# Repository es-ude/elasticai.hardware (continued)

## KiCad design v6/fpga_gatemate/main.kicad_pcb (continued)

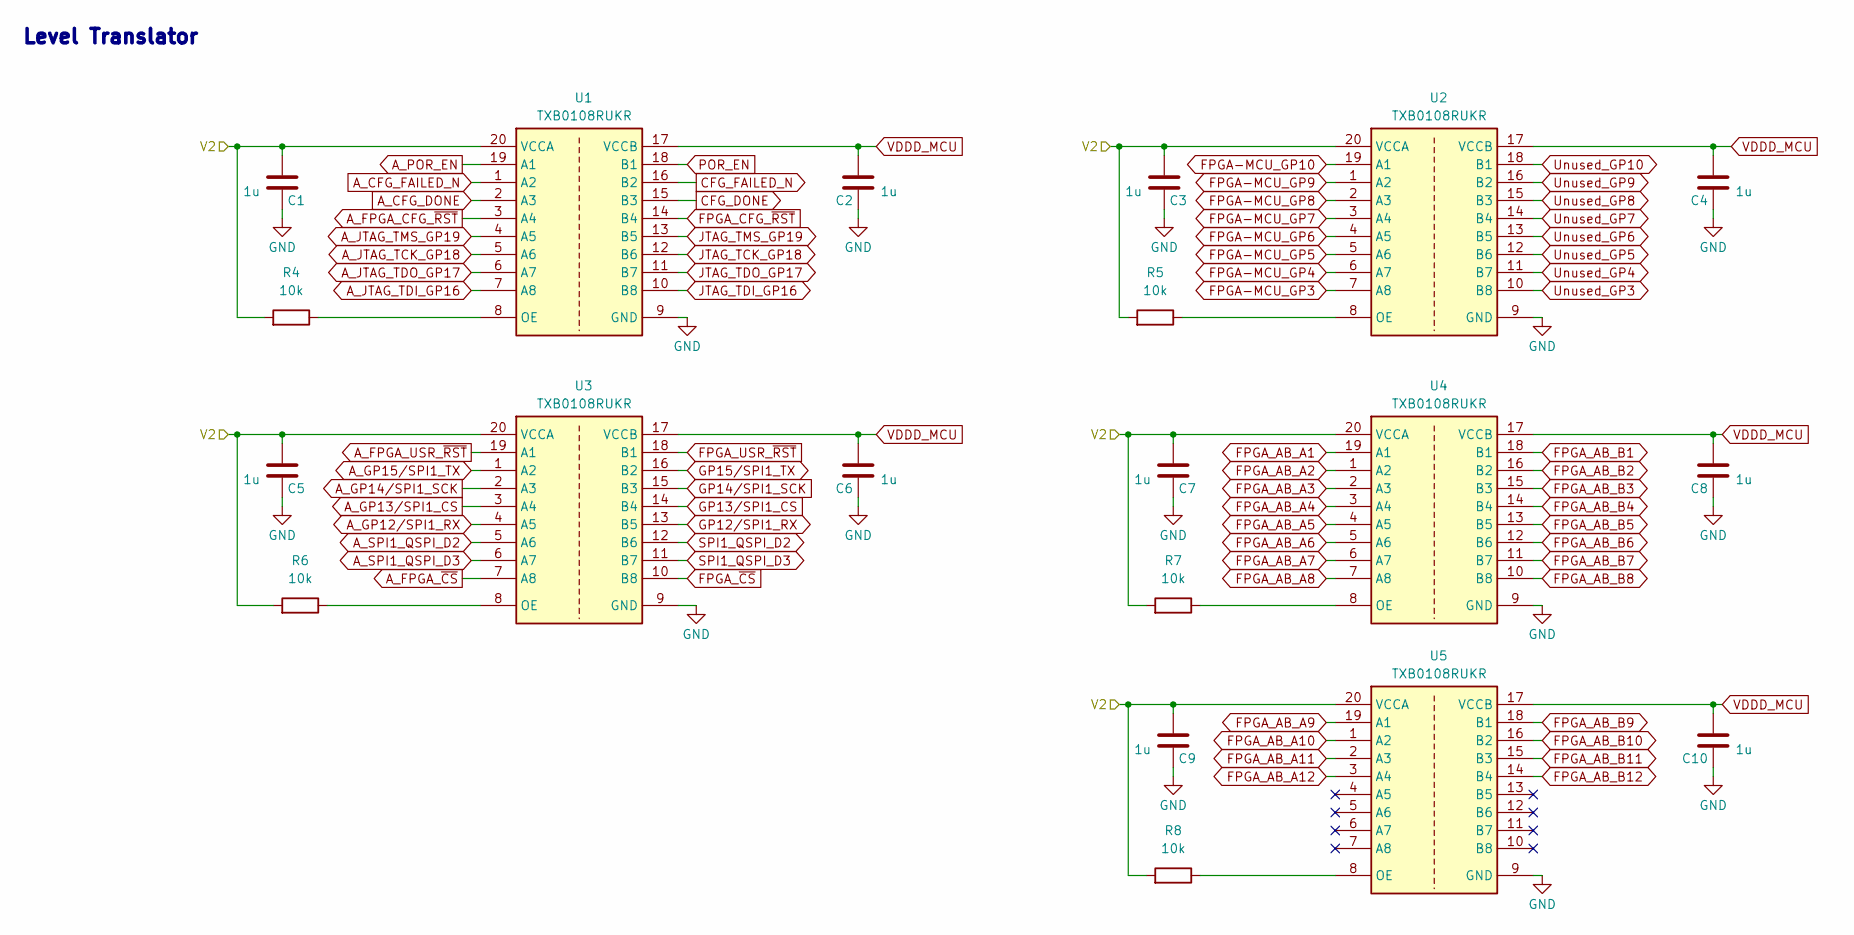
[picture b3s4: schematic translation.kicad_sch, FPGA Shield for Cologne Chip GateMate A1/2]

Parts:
C1, C2, C3, C4, C5, C6, C7, C8, C9, C10: 1u; C_0402_1005Metric
R4, R5, R6, R7, R8: 10k; R_0402_1005Metric
U1, U2, U3, U4, U5: TXB0108RUKR; WQFN-20-1EP_3x3mm_P0.4mm_EP1.7x1.7mm_TI_RUK0020; Manufacturer_Part_Number TXB0108RUKR

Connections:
/2V5: C1.2, C3.2, C5.2, C7.2, C9.2, R4.2, R5.2, R6.2, R7.2, R8.2, U1.20 (VCCA), U2.20 (VCCA), U3.20 (VCCA), U4.20 (VCCA), U5.20 (VCCA); also elsewhere on the board
A_CFG_DONE: U1.2 (A3); also elsewhere on the board
A_CFG_FAILED_N: U1.1 (A2); also elsewhere on the board
A_FPGA_CFG_~RST: U1.3 (A4); also elsewhere on the board
A_FPGA_USR_~RST: U3.19 (A1); also elsewhere on the board
A_FPGA_~CS: U3.7 (A8); also elsewhere on the board
A_GP12/SPI1_RX: U3.4 (A5); also elsewhere on the board
A_GP13/SPI1_CS: U3.3 (A4); also elsewhere on the board
A_GP14/SPI1_SCK: U3.2 (A3); also elsewhere on the board
A_GP15/SPI1_TX: U3.1 (A2); also elsewhere on the board
A_JTAG_TCK_GP18: U1.5 (A6); also elsewhere on the board
A_JTAG_TDI_GP16: U1.7 (A8); also elsewhere on the board
A_JTAG_TDO_GP17: U1.6 (A7); also elsewhere on the board
A_JTAG_TMS_GP19: U1.4 (A5); also elsewhere on the board
A_POR_EN: U1.19 (A1); also elsewhere on the board
A_SPI1_QSPI_D2: U3.5 (A6); also elsewhere on the board
A_SPI1_QSPI_D3: U3.6 (A7); also elsewhere on the board
CFG_DONE: U1.15 (B3); also elsewhere on the board
CFG_FAILED_N: U1.16 (B2); also elsewhere on the board
FPGA-MCU_GP3: U2.7 (A8); also elsewhere on the board
FPGA-MCU_GP4: U2.6 (A7); also elsewhere on the board
FPGA-MCU_GP5: U2.5 (A6); also elsewhere on the board
FPGA-MCU_GP6: U2.4 (A5); also elsewhere on the board
FPGA-MCU_GP7: U2.3 (A4); also elsewhere on the board
FPGA-MCU_GP8: U2.2 (A3); also elsewhere on the board
FPGA-MCU_GP9: U2.1 (A2); also elsewhere on the board
FPGA-MCU_GP10: U2.19 (A1); also elsewhere on the board
FPGA_AB_A1: U4.19 (A1); also elsewhere on the board
FPGA_AB_A2: U4.1 (A2); also elsewhere on the board
FPGA_AB_A3: U4.2 (A3); also elsewhere on the board
FPGA_AB_A4: U4.3 (A4); also elsewhere on the board
FPGA_AB_A5: U4.4 (A5); also elsewhere on the board
FPGA_AB_A6: U4.5 (A6); also elsewhere on the board
FPGA_AB_A7: U4.6 (A7); also elsewhere on the board
FPGA_AB_A8: U4.7 (A8); also elsewhere on the board
FPGA_AB_A9: U5.19 (A1); also elsewhere on the board
FPGA_AB_A10: U5.1 (A2); also elsewhere on the board
FPGA_AB_A11: U5.2 (A3); also elsewhere on the board
FPGA_AB_A12: U5.3 (A4); also elsewhere on the board
FPGA_AB_B1: U4.18 (B1); also elsewhere on the board
FPGA_AB_B2: U4.16 (B2); also elsewhere on the board
FPGA_AB_B3: U4.15 (B3); also elsewhere on the board
FPGA_AB_B4: U4.14 (B4); also elsewhere on the board
FPGA_AB_B5: U4.13 (B5); also elsewhere on the board
FPGA_AB_B6: U4.12 (B6); also elsewhere on the board
FPGA_AB_B7: U4.11 (B7); also elsewhere on the board
FPGA_AB_B8: U4.10 (B8); also elsewhere on the board
FPGA_AB_B9: U5.18 (B1); also elsewhere on the board
FPGA_AB_B10: U5.16 (B2); also elsewhere on the board
FPGA_AB_B11: U5.15 (B3); also elsewhere on the board
FPGA_AB_B12: U5.14 (B4); also elsewhere on the board
FPGA_CFG_~RST: U1.14 (B4); also elsewhere on the board
FPGA_USR_~RST: U3.18 (B1); also elsewhere on the board
FPGA_~CS: U3.10 (B8); also elsewhere on the board
GND: C1.1, C2.1, C3.1, C4.1, C5.1, C6.1, C7.1, C8.1, C9.1, C10.1, U1.9 (GND), U1.21 (GND), U2.9 (GND), U2.21 (GND), U3.9 (GND), U3.21 (GND), U4.9 (GND), U4.21 (GND), U5.9 (GND), U5.21 (GND); also elsewhere on the board
GP12/SPI1_RX: U3.13 (B5); also elsewhere on the board
GP13/SPI1_CS: U3.14 (B4); also elsewhere on the board
GP14/SPI1_SCK: U3.15 (B3); also elsewhere on the board
GP15/SPI1_TX: U3.16 (B2); also elsewhere on the board
JTAG_TCK_GP18: U1.12 (B6); also elsewhere on the board
JTAG_TDI_GP16: U1.10 (B8); also elsewhere on the board
JTAG_TDO_GP17: U1.11 (B7); also elsewhere on the board
JTAG_TMS_GP19: U1.13 (B5); also elsewhere on the board
unnamed: R4.1, U1.8 (OE)
unnamed: R5.1, U2.8 (OE)
unnamed: R6.1, U3.8 (OE)
unnamed: R7.1, U4.8 (OE)
unnamed: R8.1, U5.8 (OE)
POR_EN: U1.18 (B1); also elsewhere on the board
SPI1_QSPI_D2: U3.12 (B6); also elsewhere on the board
SPI1_QSPI_D3: U3.11 (B7); also elsewhere on the board
Unused_GP3: U2.10 (B8); also elsewhere on the board
Unused_GP4: U2.11 (B7); also elsewhere on the board
Unused_GP5: U2.12 (B6); also elsewhere on the board
Unused_GP6: U2.13 (B5); also elsewhere on the board
Unused_GP7: U2.14 (B4); also elsewhere on the board
Unused_GP8: U2.15 (B3); also elsewhere on the board
Unused_GP9: U2.16 (B2); also elsewhere on the board
Unused_GP10: U2.18 (B1); also elsewhere on the board
VDDD_MCU: C2.2, C4.2, C6.2, C8.2, C10.2, U1.17 (VCCB), U2.17 (VCCB), U3.17 (VCCB), U4.17 (VCCB), U5.17 (VCCB); also elsewhere on the board

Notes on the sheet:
Level Translator

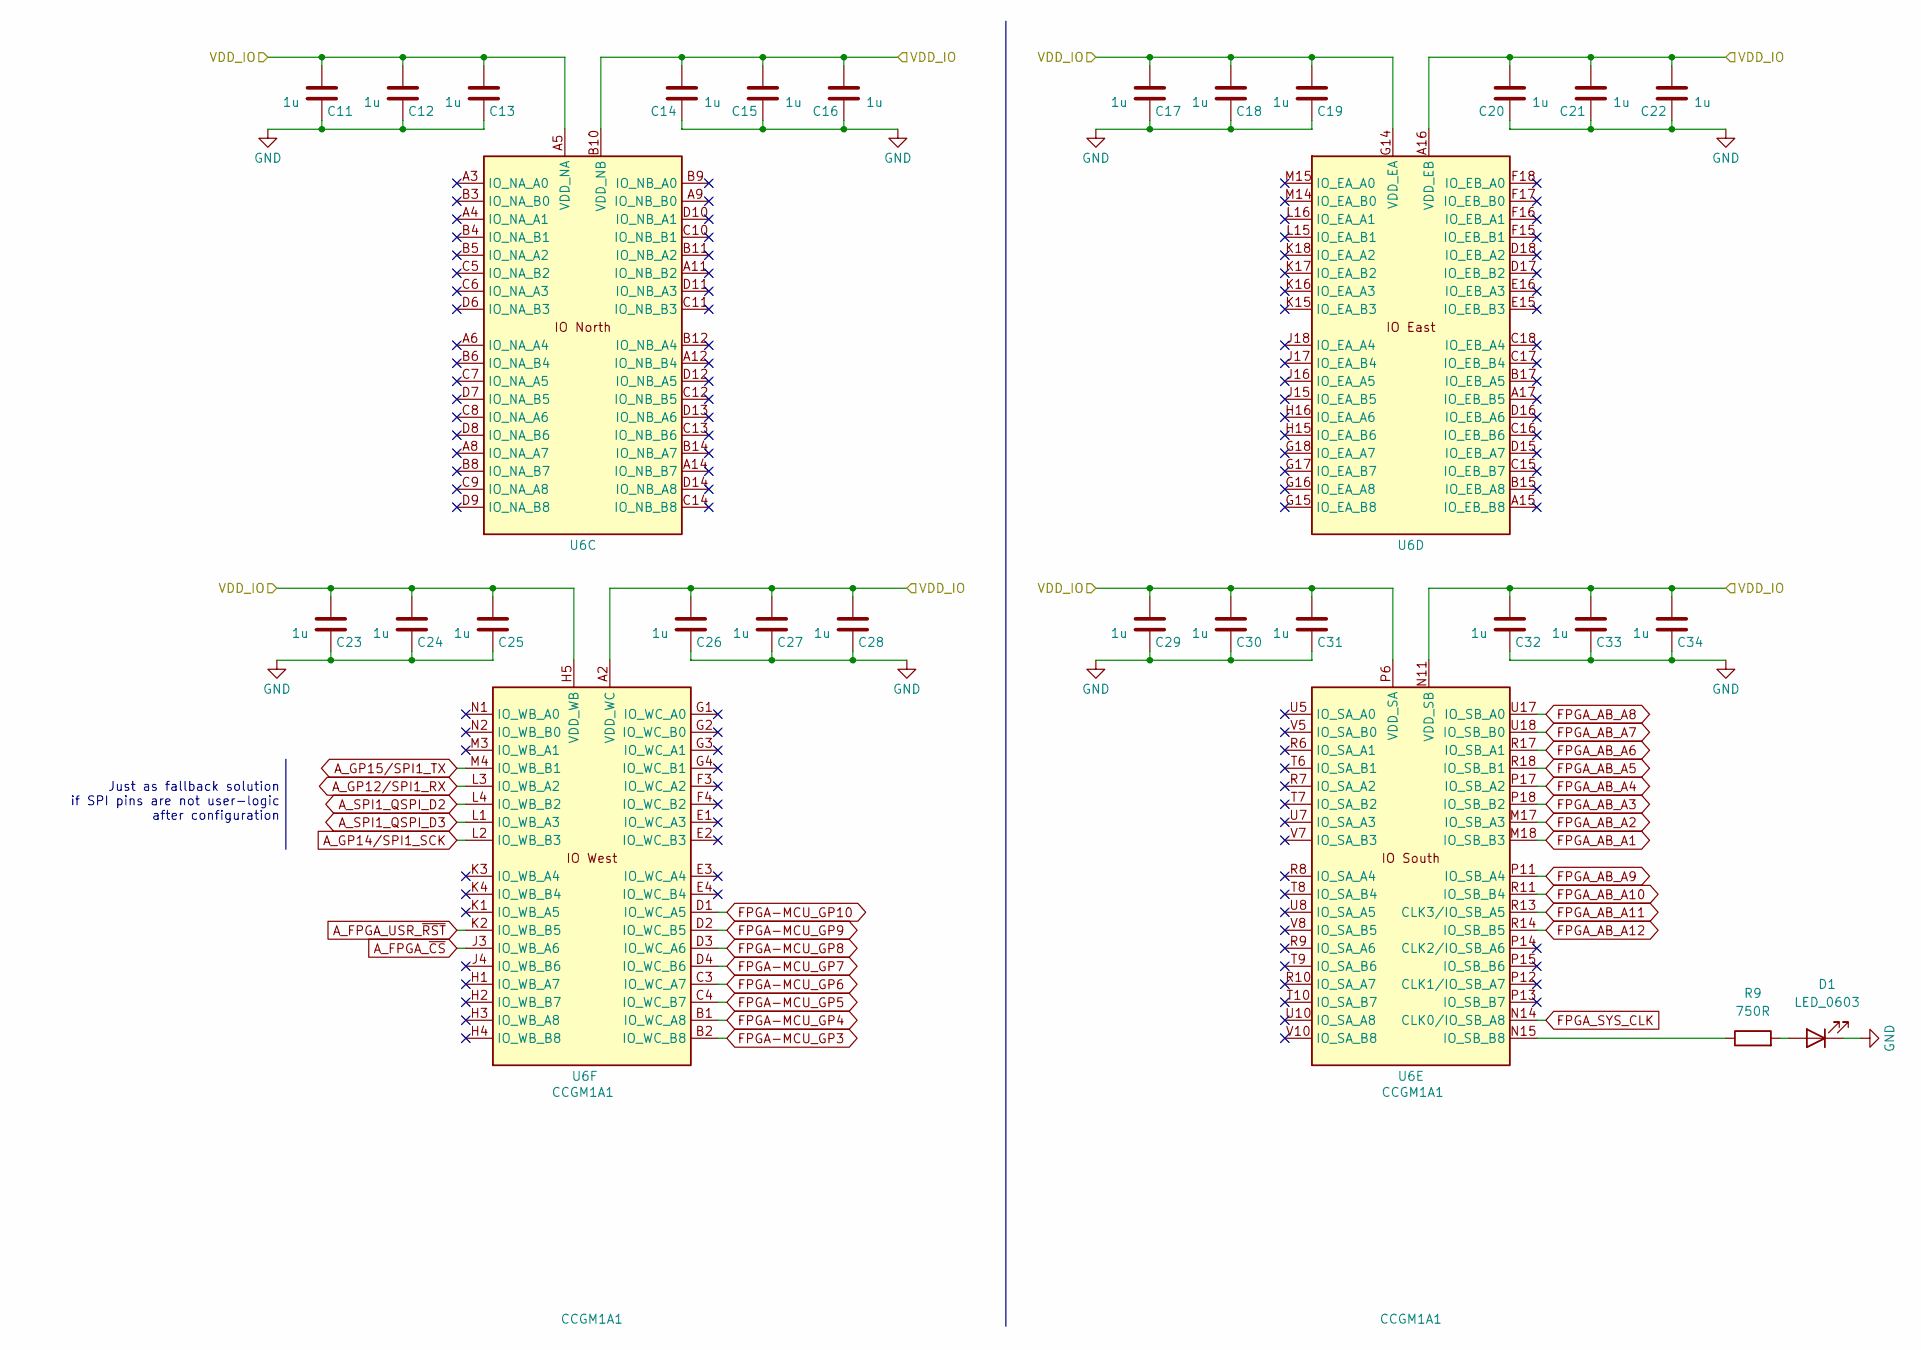
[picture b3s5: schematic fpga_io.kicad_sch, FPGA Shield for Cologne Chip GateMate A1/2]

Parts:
C11, C12, C13, C14, C15, C16, C17, C18, C19, C20, C21, C22, C23, C24, C25, C26, C27, C28, C29, C30, C31, C32, C33, C34: 1u; C_0402_1005Metric
D1: LED_0603; LED_0603_1608Metric
R9: 750R; R_0402_1005Metric
U6: CCGM1A1; BGA-324_15.0x15.0mm_Layout18x18_P0.8mm_Ball0.5mm_Pad0.4mm_N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

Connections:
/2V5: C11.2, C12.2, C13.2, C14.2, C15.2, C16.2, C17.2, C18.2, C19.2, C20.2, C21.2, C22.2, C23.2, C24.2, C25.2, C26.2, C27.2, C28.2, C29.2, C30.2, C31.2, C32.2, C33.2, C34.2, U6.A2 (VDD_WC), U6.A5 (VDD_NA), U6.A16 (VDD_EB), U6.B7 (VDD_NA), U6.B10 (VDD_NB), U6.B13 (VDD_NB), U6.B18 (VDD_EB), U6.C2 (VDD_WC), U6.D5 (VDD_WC), U6.E6 (VDD_NA), U6.E8 (VDD_NA), U6.E10 (VDD_NB), U6.E12 (VDD_NB), U6.E14 (VDD_EB), U6.E17 (VDD_EB), U6.F2 (VDD_WC), U6.F5 (VDD_WC), U6.F7 (VDD_NA), U6.F11 (VDD_NB), U6.F13 (VDD_EB), U6.G14 (VDD_EA), U6.H5 (VDD_WB), U6.H17 (VDD_EA), U6.J2 (VDD_WB), U6.J14 (VDD_EA), U6.K5 (VDD_WB), U6.L14 (VDD_EA), U6.L17 (VDD_EA), U6.M2 (VDD_WB), U6.M5 (VDD_WB), U6.N11 (VDD_SB), U6.N13 (VDD_SB), U6.N18 (VDD_SB), U6.P6 (VDD_SA), U6.P8 (VDD_SA), U6.P10 (VDD_SA), U6.R15 (VDD_SB), U6.T18 (VDD_SB), U6.U6 (VDD_SA), U6.U9 (VDD_SA); also elsewhere on the board
A_FPGA_USR_~RST: U6.K2 (IO_WB_B5); also elsewhere on the board
A_FPGA_~CS: U6.J3 (IO_WB_A6); also elsewhere on the board
A_GP12/SPI1_RX: U6.L3 (IO_WB_A2); also elsewhere on the board
A_GP14/SPI1_SCK: U6.L2 (IO_WB_B3); also elsewhere on the board
A_GP15/SPI1_TX: U6.M4 (IO_WB_B1); also elsewhere on the board
A_SPI1_QSPI_D2: U6.L4 (IO_WB_B2); also elsewhere on the board
A_SPI1_QSPI_D3: U6.L1 (IO_WB_A3); also elsewhere on the board
FPGA-MCU_GP3: U6.B2 (IO_WC_B8); also elsewhere on the board
FPGA-MCU_GP4: U6.B1 (IO_WC_A8); also elsewhere on the board
FPGA-MCU_GP5: U6.C4 (IO_WC_B7); also elsewhere on the board
FPGA-MCU_GP6: U6.C3 (IO_WC_A7); also elsewhere on the board
FPGA-MCU_GP7: U6.D4 (IO_WC_B6); also elsewhere on the board
FPGA-MCU_GP8: U6.D3 (IO_WC_A6); also elsewhere on the board
FPGA-MCU_GP9: U6.D2 (IO_WC_B5); also elsewhere on the board
FPGA-MCU_GP10: U6.D1 (IO_WC_A5); also elsewhere on the board
FPGA_AB_A1: U6.M18 (IO_SB_B3); also elsewhere on the board
FPGA_AB_A2: U6.M17 (IO_SB_A3); also elsewhere on the board
FPGA_AB_A3: U6.P18 (IO_SB_B2); also elsewhere on the board
FPGA_AB_A4: U6.P17 (IO_SB_A2); also elsewhere on the board
FPGA_AB_A5: U6.R18 (IO_SB_B1); also elsewhere on the board
FPGA_AB_A6: U6.R17 (IO_SB_A1); also elsewhere on the board
FPGA_AB_A7: U6.U18 (IO_SB_B0); also elsewhere on the board
FPGA_AB_A8: U6.U17 (IO_SB_A0); also elsewhere on the board
FPGA_AB_A9: U6.P11 (IO_SB_A4); also elsewhere on the board
FPGA_AB_A10: U6.R11 (IO_SB_B4); also elsewhere on the board
FPGA_AB_A11: U6.R13 (CLK3/IO_SB_A5); also elsewhere on the board
FPGA_AB_A12: U6.R14 (IO_SB_B5); also elsewhere on the board
FPGA_SYS_CLK: U6.N14 (CLK0/IO_SB_A8); also elsewhere on the board
GND: C11.1, C12.1, C13.1, C14.1, C15.1, C16.1, C17.1, C18.1, C19.1, C20.1, C21.1, C22.1, C23.1, C24.1, C25.1, C26.1, C27.1, C28.1, C29.1, C30.1, C31.1, C32.1, C33.1, C34.1, D1.1 (K); also elsewhere on the board
unnamed: D1.2 (A), R9.2
unnamed: R9.1, U6.N15 (IO_SB_B8)

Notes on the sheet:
Just as fallback solution if SPI pins are not user-logic after configuration

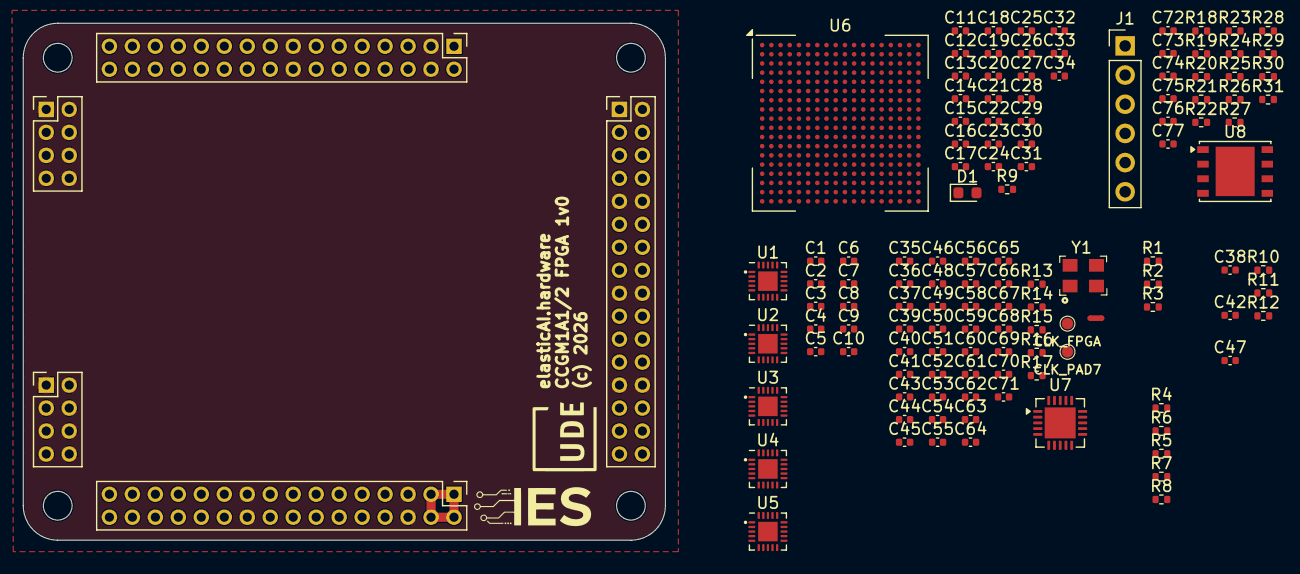
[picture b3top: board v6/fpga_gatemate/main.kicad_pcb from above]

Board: 4 copper layers, 55.9 x 45.0 mm, 123 parts (0 on the bottom side), 113 nets.

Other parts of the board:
B1: ExtensionBoard_ENv6
R1, R2: 750R; R_0402_1005Metric
R3: 27R; R_0402_1005Metric

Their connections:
/1V0: B1.C3, B1.C4, B1.C5, B1.C6, B1.C7, B1.C8; also elsewhere on the board
/2V5: B1.C11, B1.C12, B1.C13, B1.C14, B1.C15, B1.C16; also elsewhere on the board
/Connectors/FPGA_DTCT: B1.B22, R1.1
CFG_DONE: B1.A25; also elsewhere on the board
CFG_FAILED_N: B1.A28; also elsewhere on the board
EN_FPGA_OSC: B1.A13; also elsewhere on the board
FPGA_AB_B1: B1.B8; also elsewhere on the board
FPGA_AB_B2: B1.B7; also elsewhere on the board
FPGA_AB_B3: B1.B10; also elsewhere on the board
FPGA_AB_B4: B1.B9; also elsewhere on the board
FPGA_AB_B5: B1.B12; also elsewhere on the board
FPGA_AB_B6: B1.B11; also elsewhere on the board
FPGA_AB_B7: B1.B14; also elsewhere on the board
FPGA_AB_B8: B1.B13; also elsewhere on the board
FPGA_AB_B9: B1.B16; also elsewhere on the board
FPGA_AB_B10: B1.B15; also elsewhere on the board
FPGA_AB_B11: B1.B18; also elsewhere on the board
FPGA_AB_B12: B1.B17; also elsewhere on the board
FPGA_CFG_~RST: B1.A26; also elsewhere on the board
FPGA_USR_~RST: B1.A24; also elsewhere on the board
FPGA_~CS: B1.A14; also elsewhere on the board
GND: B1.A3, B1.A4, B1.A15, B1.A16, B1.B5, B1.B6, B1.B19, B1.B20, B1.C1, B1.C2, B1.C9, B1.C10, B1.C17, B1.C18, B1.C25, B1.C26, B1.D1, B1.D2, B1.D3, B1.D4, B1.D5, B1.D6, B1.D7, B1.D8, B1.E1, B1.E2, B1.E3, B1.E4, B1.E5, B1.E6, B1.E7, B1.E8, R3.2; also elsewhere on the board
GP0/I2C0_SDA: B1.A2; also elsewhere on the board
GP1/I2C0_SCL: B1.A1; also elsewhere on the board
GP12/SPI1_RX: B1.A18; also elsewhere on the board
GP13/SPI1_CS: B1.A17; also elsewhere on the board
GP14/SPI1_SCK: B1.A20; also elsewhere on the board
GP15/SPI1_TX: B1.A19; also elsewhere on the board
JTAG_TCK_GP18: B1.A30; also elsewhere on the board
JTAG_TDI_GP16: B1.A32; also elsewhere on the board
JTAG_TDO_GP17: B1.A29; also elsewhere on the board
JTAG_TMS_GP19: B1.A31; also elsewhere on the board
unnamed: R1.2, R2.1
unnamed: R2.2, R3.1
POR_EN: B1.A27; also elsewhere on the board
SPI1_QSPI_D2: B1.A22; also elsewhere on the board
SPI1_QSPI_D3: B1.A21; also elsewhere on the board
Unused_GP3: B1.A6; also elsewhere on the board
Unused_GP4: B1.A5; also elsewhere on the board
Unused_GP5: B1.A8; also elsewhere on the board
Unused_GP6: B1.A7; also elsewhere on the board
Unused_GP7: B1.A10; also elsewhere on the board
Unused_GP8: B1.A9; also elsewhere on the board
Unused_GP9: B1.A12; also elsewhere on the board
Unused_GP10: B1.A11; also elsewhere on the board
VDDD_MCU: B1.A23; also elsewhere on the board
VSYS_EX: B1.B1, B1.B2, B1.B3, B1.B4

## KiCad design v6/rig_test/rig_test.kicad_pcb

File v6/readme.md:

# Elastic Node Hardware Platform v6 (ENv6)

This folder contains the hardware designs (KiCad) and documentation of the Elastic Node v6 platform.

- Firmware: the elasticAI.runtime ENv5 [repo](https://github.com/es-ude/elastic-ai.runtime.enV5) can be used as a starting point. An extension for ENv6 is coming.
- Control from a PC (Python CLI): [elasticAI.experiment-framework](https://github.com/es-ude/elastic-ai.experiment-framework).
- Connector symbols and footprints are part of our [KiCad library](https://github.com/es-ude/kicad-library).

## Concept

ENv6 is a **modular stack** for running and measuring neural-network accelerators on small FPGAs in an energy-constrained setting. The ENv5 monolith is split into three swappable layers that are connected through standardized board-to-board headers:

| Layer                            | Purpose                                                                                                                                                            | Folder                                                                                                                           |
|----------------------------------|--------------------------------------------------------------------------------------------------------------------------------------------------------------------|----------------------------------------------------------------------------------------------------------------------------------|
| **Base board**                   | RP2354B MCU, Raspberry Pi radio module (WLAN), USB-C, Li-ion charger, programmable power supply, 4-channel current sensor (PAC1954), microSD, WS2812B status LED   | [`main`](main/readme.md)                                                                                                         |
| **FPGA board** (swappable)       | One FPGA (+ configuration flash, clock, level shifting as needed); identifies itself to the MCU with an ID resistor                                                | [`fpga_lattice`](fpga_lattice/readme.md), [`fpga_gatemate`](fpga_gatemate/readme.md), [`fpga_spartan7`](fpga_spartan7/readme.md) |
| **Application board** (optional) | Sensors, actuators or measurement hardware; identifies itself with an ID resistor                                                                                  | [`adapter_ppk2`](adapter_ppk2/readme.md)                                                                                         |

The MCU configures the FPGA (flash/bitstream over SPI1, JTAG, configuration lines), supplies it with four programmable supply rails (`PSU1 … PSU4`) and measures their current. The attached FPGA and application boards are detected automatically (see [Auto-identification](#auto-identification-of-connected-boards)).

In addition, [`mini`](mini/readme.md) is a single-board version (see [ENv6.mini](#env6mini)) and [`1_dev_artix`](1_dev_artix/readme.md) is a stand-alone Artix-7 development board.

## State

Still in development. Overview of the boards in this folder:

| Board                            | Folder                           | State          | Infos                                                                                                |
|----------------------------------|----------------------------------|----------------|------------------------------------------------------------------------------------------------------|
| Base board                       | [`main`](main)                   | In development | [readme](main/readme.md), [iBOM](main/bom/ibom.html)                                                 |
| PPK2 measurement adapter         | [`adapter_ppk2`](adapter_ppk2)   | In development | [readme](adapter_ppk2/readme.md)                                                                     |
| FPGA board Lattice iCE40UP5K     | [`fpga_lattice`](fpga_lattice)   | In development | [readme](fpga_lattice/readme.md), [iBOM](fpga_lattice/bom/ibom.html)                                 |
| FPGA board GateMate M1A1         | [`fpga_gatemate`](fpga_gatemate) | In development | [readme](fpga_gatemate/readme.md)                                                                    |
| FPGA board GateMate M1A2         | –                                | In development | –                                                                                                    |
| FPGA board Spartan-7 (S15 / S50) | [`fpga_spartan7`](fpga_spartan7) | In development | [readme](fpga_spartan7/readme.md)                                                                    |
| FPGA board Artix-7 100T          | –                                | Not started    | –                                                                                                    |
| Artix-7 development board        | [`1_dev_artix`](1_dev_artix)     | Deprecated     | [readme](1_dev_artix/readme.md), [iBOM](1_dev_artix/bom/ibom.html)                                   |
| **ENv6.mini** (iCE40UP5K)        | [`mini`](mini)                   | Active         | [readme](mini/readme.md), [iBOM v1.1](mini/bom/ibom_1v1.html), [v1.0](mini/bom/ibom_1v0.html)        |

## Changes to ENv5
### Improvements
- Removed the ESP32 and replaced it with a Raspberry Pi radio module.
- Upgraded the MCU from RP2040 to RP2354B (more GPIOs). The variant with internal flash is optional (external W25Q16 flash is on the board).
- Upgraded the current sensor from PAC1934 to PAC1954 (four channels on the base board).
- Refactored the power path: new battery charger (BQ25188), programmable 4-output power IC (LP873300), 3.3 V LDO for the MCU.
- Removed all status LEDs of the base board and replaced them with a single WS2812B. (FPGA boards may carry their own status LED.)
- More debugging features towards the FPGA (JTAG, configuration/status lines, ...).
- Reduced the number of SPI buses to the FPGA (SPI1 is shared between flashing and user logic).
- More GPIOs towards the FPGA board.

### New features
- JTAG towards the FPGA board via an external probe on the base board header. Running DirtyJTAG on the MCU is planned (the schematic marks the external header as a temporary solution until then).
- Header with unused MCU GPIOs for applications.
- Split into base board (MCU, WLAN, USB, power, PAC sensor), optional application board and swappable FPGA board.
- Automatic identification of the connected FPGA board and application board (see below).
- microSD card slot (SPI0 of the MCU).
- Pin headers to route the supply rails through an external high-speed current measurement unit (e.g. Nordic PPK2) instead of the on-board PAC1954.

## Auto-identification of connected boards

The base board identifies which swappable FPGA board and which optional application board is attached. Each board carries one resistor to GND (`R_down`); on the base board a 10 kΩ pull-up (`R_up`) to `VDD_MCU` forms a divider that is sampled by the 12-bit ADC of the RP2354B (`FPGA_DETECT` on GP46/ADC6 for the FPGA board, `APP_DETECT` on GP47/ADC7 for the application board, each with a 1 µF capacitor to GND). `VDD_MCU` also supplies `AVDD_ADC`, so the measurement is ratiometric.

Assumptions: 1 % resistors (E12 values), 12-bit ADC, total noise/offset/INL error ±16 LSB, 16× oversampling. For the worst-case tolerance of both resistors plus ±16 LSB, the minimum gap between windows is ~73 LSB. Because of the 10 kΩ / 1 µF RC filter (τ ≈ 10 ms), wait at least ~50 ms after power-up before sampling.

### Setup

```
 VDD_MCU (3.3 V)
     |
   [R_up = 10 kΩ, 1 %]       <- base board (fixed)
     |
     +------ ADC pin (+ 1 µF to GND)
     |
   [R_down = ID resistor]    <- FPGA / application board (unique per board)
     |
    GND
```
`Code = 4095 · R_down / (R_down + R_up)`

### ID table for the FPGA boards

| ID   | R_down          | Nominal code | Window (min … max)   | Target                    |
|------|-----------------|--------------|----------------------|---------------------------|
| –    | short to GND    | 0            | 0 … 16 → fault       | None                      |
| 1    | 1.0 kΩ          | 372          | 350 … 395            | Lattice iCE40UP5K         |
| 2    | 1.5 kΩ          | 534          | 509 … 560            | CologneChip GateMate M1A1 |
| 3    | 2.2 kΩ          | 738          | 710 … 767            | CologneChip GateMate M1A2 |
| 4    | 3.3 kΩ          | 1016         | 985 … 1047           | reserved                  |
| 5    | 4.7 kΩ          | 1309         | 1275 … 1343          | reserved                  |
| 6    | 6.8 kΩ          | 1658         | 1622 … 1693          | reserved                  |
| 7    | 10 kΩ           | 2048         | 2011 … 2084          | AMD Spartan-7 S15         |
| 8    | 15 kΩ           | 2457         | 2421 … 2493          | AMD Spartan-7 S50         |
| 9    | 22 kΩ           | 2815         | 2781 … 2849          | AMD Artix-7 100T          |
| 10   | 33 kΩ           | 3143         | 3112 … 3173          | reserved                  |
| 11   | 47 kΩ           | 3377         | 3349 … 3404          | reserved                  |
| 12   | 68 kΩ           | 3570         | 3545 … 3595          | reserved                  |
| 13   | 100 kΩ          | 3723         | 3700 … 3745          | reserved                  |
| 14   | 150 kΩ          | 3839         | 3818 … 3860          | reserved                  |
| –    | open (no board) | ≈ 4095       | > 3900 → no board    | None                      |

### ID table for the application boards

| ID   | R_down          | Nominal code | Window (min … max)   | Target                            |
|------|-----------------|--------------|----------------------|-----------------------------------|
| –    | short to GND    | 0            | 0 … 16 → fault       | None                              |
| 1    | 1.0 kΩ          | 372          | 350 … 395            | Measurement board for Nordic PPK2 |
| 7    | 10 kΩ           | 2048         | 2011 … 2084          | Real application board            |
| –    | open (no board) | ≈ 4095       | > 3900 → no board    | None                              |

## Connector of the base board

The base board connects to the other boards with four headers (KiCad symbol `ENv6_Custom_Symbols:BaseBoard_ENv6`, footprint `ENv6_Custom_Footprints:BaseBoard_ENv6`, instance `B401` in [`main/connector.kicad_sch`](main/connector.kicad_sch)). The tables below are generated from that schematic (pin → net → MCU pin).

- **MCU/FPGA header** (A1 … A32): I2C0, SPI1, JTAG, configuration lines and general-purpose MCU GPIOs towards the FPGA board.
- **Application header** (B1 … B32): `VSYS`, detection lines, MCU GPIOs/ADC inputs for the application board and `VDD_MCU`. Pins B7 … B18 do not exist on the base-board symbol. According to the schematics of the FPGA boards, the FPGA IOs for the application board are provided by the FPGA board itself (B row of the `FPGABoard_ENv6` symbol).
- **Power header** (C1 … C32): the four programmable rails of the LP873300 (`PSU1 … PSU4`, six pins each, separated by GND pins). Their use (core, auxiliary, bank, ...) is defined by the FPGA board. All four rails pass the PAC1954 current sensor (or an external PPK2).
- **GND headers** (D1 … D8, E1 … E8): additional ground connections.

### MCU/FPGA header
| Pin | Net              | MCU pin | Function                                                                      |
|-----|------------------|---------|-------------------------------------------------------------------------------|
| A1  | I2C0_SCL         | GP1     | I2C clock                                                                     |
| A2  | I2C0_SDA         | GP0     | I2C data                                                                      |
| A3  | GND              |         | Ground                                                                        |
| A4  | GND              |         | Ground                                                                        |
| A5  | Unused_GP3       | GP3     | General-purpose MCU GPIO                                                      |
| A6  | Unused_GP2       | GP2     | General-purpose MCU GPIO                                                      |
| A7  | Unused_GP5       | GP5     | General-purpose MCU GPIO                                                      |
| A8  | Unused_GP4       | GP4     | General-purpose MCU GPIO                                                      |
| A9  | Unused_GP7       | GP7     | General-purpose MCU GPIO                                                      |
| A10 | Unused_GP6       | GP6     | General-purpose MCU GPIO                                                      |
| A11 | Unused_GP9       | GP9     | General-purpose MCU GPIO                                                      |
| A12 | Unused_GP8       | GP8     | General-purpose MCU GPIO                                                      |
| A13 | MCU-FPGA_EN_OSC  | GP11    | Enable for the FPGA oscillator                                                |
| A14 | MCU-FPGA_CS      | GP10    | Additional chip select towards the FPGA                                       |
| A15 | GND              |         | Ground                                                                        |
| A16 | GND              |         | Ground                                                                        |
| A17 | SPI1_CS          | GP13    | SPI1 chip select                                                              |
| A18 | SPI1_RX          | GP12    | SPI1 RX (MISO from the MCU perspective)                                       |
| A19 | SPI1_TX          | GP15    | SPI1 TX (MOSI from the MCU perspective)                                       |
| A20 | SPI1_SCK         | GP14    | SPI1 clock                                                                    |
| A21 | QSPI_IO3         | GP17    | Quad-SPI data line 3                                                          |
| A22 | QSPI_IO2         | GP16    | Quad-SPI data line 2                                                          |
| A23 | VDD_MCU          |         | MCU I/O supply (3.3 V) as reference for driving IO signals (not for powering) |
| A24 | MCU-FPGA_USR-RST | GP18    | User reset towards the FPGA                                                   |
| A25 | FPGA_CFG_2       | GP20    | Configration Feedback with State (e.g. `DONE`)                                |
| A26 | FPGA_CFG_1       | GP19    | Configuration Reset to control the FPGA                                       |
| A27 | FPGA_CFG_4       | GP22    | Configuration for further control (like `Power-On-Reset` in CCGM1Ax)          |
| A28 | FPGA_CFG_3       | GP21    | Configuration Control Line (like `FAILED` in CCGM1Ax, or `INIT`in AMDs FPGA)  |
| A29 | JTAG_TDO         | GP27    | JTAG test data out (from the FPGA)                                            |
| A30 | JTAG_TCK         | GP26    | JTAG test clock                                                               |
| A31 | JTAG_TMS         | GP30    | JTAG test mode select                                                         |
| A32 | JTAG_TDI         | GP28    | JTAG test data in (to the FPGA)                                               |

### Application header
| Pin       | Net         | MCU pin     | Function                                                     |
|-----------|-------------|-------------|--------------------------------------------------------------|
| B1 … B4   | VSYS        |             | System voltage (battery / USB)                               |
| B5, B6    | GND         |             | Ground                                                       |
| B7 … B18  | –           |             | Not present on the base-board symbol                         |
| B19, B20  | GND         |             | Ground                                                       |
| B21       | APP_DETECT  | GP47 (ADC7) | Detection of the application board                           |
| B22       | FPGA_DETECT | GP46 (ADC6) | Detection of the FPGA board                                  |
| B23       | GP45_ADC5   | GP45        | MCU GPIO / ADC5                                              |
| B24       | GP44_ADC4   | GP44        | MCU GPIO / ADC4                                              |
| B25       | GP43_ADC3   | GP43        | MCU GPIO / ADC3                                              |
| B26       | GP42_ADC2   | GP42        | MCU GPIO / ADC2                                              |
| B27       | GP41_ADC1   | GP41        | MCU GPIO / ADC1                                              |
| B28       | GP40_ADC0   | GP40        | MCU GPIO / ADC0                                              |
| B29       | MCU-AP_GP35 | GP35        | MCU GPIO                                                     |
| B30       | MCU-AP_GP34 | GP34        | MCU GPIO                                                     |
| B31       | MCU-AP_GP33 | GP33        | MCU GPIO                                                     |
| B32       | VDD_MCU     |             | MCU I/O supply (3.3 V) as reference for IO level translation |

### Power header and GND headers
| Pin              | Net    |
|------------------|--------|
| C1, C2           | GND    |
| C3 … C8          | PSU1   |
| C9, C10          | GND    |
| C11 … C16        | PSU2   |
| C17, C18         | GND    |
| C19 … C24        | PSU4   |
| C25, C26         | GND    |
| C27 … C32        | PSU3   |
| D1 … D8, E1 … E8 | GND    |

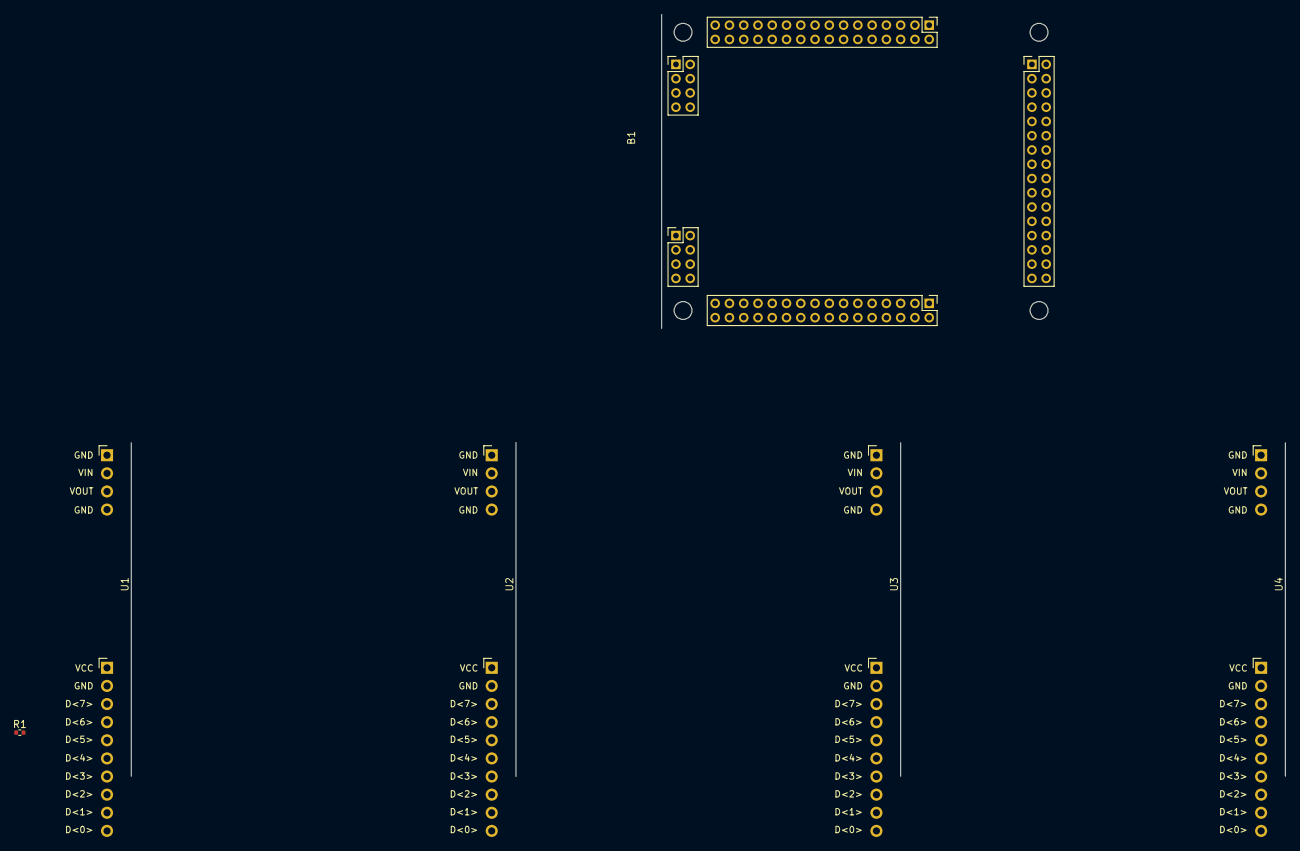
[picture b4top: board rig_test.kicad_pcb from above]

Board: 2 copper layers, 6 parts (0 on the bottom side), 11 nets, no tracks yet.

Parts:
B1: Application_ENv6
R1: 1k; R_0402_1005Metric
U1, U2, U3, U4: PPK2_CON; PPK2

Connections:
/PKK2_D0: B1.B28, U1.B10 (D0), U2.B10 (D0), U3.B10 (D0), U4.B10 (D0)
/PKK2_D1: B1.B26, U1.B9 (D1), U2.B9 (D1), U3.B9 (D1), U4.B9 (D1)
/PKK2_D2: B1.B24, U1.B8 (D2), U2.B8 (D2), U3.B8 (D2), U4.B8 (D2)
/PKK2_D3: B1.B22, U1.B7 (D3), U2.B7 (D3), U3.B7 (D3), U4.B7 (D3)
/PKK2_D4: B1.B16, U1.B6 (D4), U2.B6 (D4), U3.B6 (D4), U4.B6 (D4)
/PKK2_D5: B1.B14, U1.B5 (D5), U2.B5 (D5), U3.B5 (D5), U4.B5 (D5)
/PKK2_D6: B1.B12, U1.B4 (D6), U2.B4 (D6), U3.B4 (D6), U4.B4 (D6)
/PKK2_D7: B1.B10, U1.B3 (D7), U2.B3 (D7), U3.B3 (D7), U4.B3 (D7)
/VMCU_IO: B1.B19, U1.B1 (VCC), U2.B1 (VCC), U3.B1 (VCC), U4.B1 (VCC)
GND: B1.A3, B1.A4, B1.A13, B1.A14, B1.A31, B1.A32, B1.B5, B1.B6, B1.B20, B1.C1, B1.C2, B1.C9, B1.C10, B1.C17, B1.C18, B1.C25, B1.C26, B1.D1, B1.D2, B1.D3, B1.D4, B1.D5, B1.D6, B1.D7, B1.D8, B1.E1, B1.E2, B1.E3, B1.E4, B1.E5, B1.E6, B1.E7, B1.E8, R1.1, U1.A1 (GND), U1.A4 (GND), U1.B2 (GND), U2.A1 (GND), U2.A4 (GND), U2.B2 (GND), U3.A1 (GND), U3.A4 (GND), U3.B2 (GND), U4.A1 (GND), U4.A4 (GND), U4.B2 (GND)
unnamed: B1.B17, R1.2

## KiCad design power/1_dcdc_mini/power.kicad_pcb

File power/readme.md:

# Elastic Power Modules
This folder includes three different version of power supply modules to build bipolar power supplies for custom boards. 
The corresponding KiCAD symbols and layouts are in our KiCAD-library ([Link](https://github.com/es-ude/kicad-library)).

## Version: External Power Supply
This board allows to connect an external power supply to this board using the Banana connectors.
A bill of materials (BOM) can be open here ([Link](2_ext_supply/bom/ibom.html)). Please open it via: Open in new tab.

## Version: DC/DC Power Supply (up to +/- 6V)
This board allows to generate a bipolar power supply on the board using small DC/DC converters.
A BOM can be open here ([Link](1_dcdc_mini/bom/ibom.html)). Please open it via: Open in new tab.

## Version: DC/DC Power Supply (up to +/- 20V)
This board allows to generate a bipolar power supply on the board using large DC/DC converters.
A BOM can be open here ([Link](0_dcdc_max/bom/ibom.html)). Please open it via: Open in new tab.

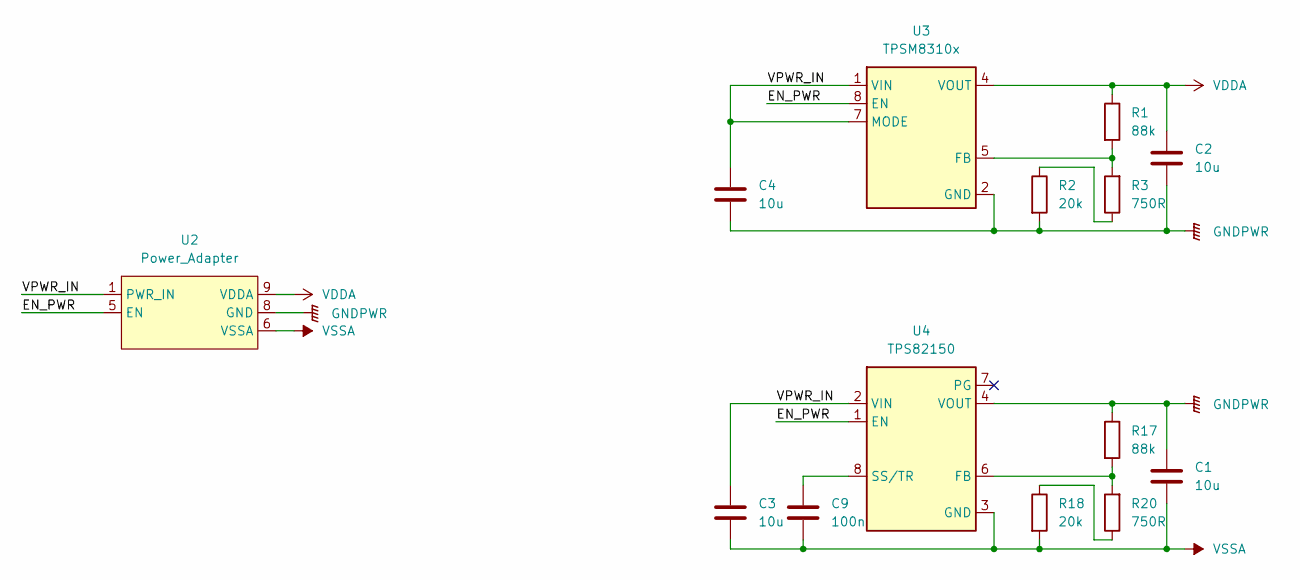
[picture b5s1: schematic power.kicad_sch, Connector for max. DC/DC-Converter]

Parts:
C1, C2, C3, C4: 10u; C_0805_2012Metric
C9: 100n; C_0402_1005Metric
R1, R17: 88k; R_0402_1005Metric
R2, R18: 20k; R_0402_1005Metric
R3, R20: 750R; R_0402_1005Metric
U2: Power_Adapter; power_adapter
U3: TPSM8310x; MICROSIP8_SIU_TEX
U4: TPS82150; Texas_SIL0008D_MicroSiP-8-1EP_2.8x3mm_P0.65mm_EP1.1x1.9mm

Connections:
/EN_PWR: U2.5 (EN), U3.8 (EN), U4.1 (EN)
/VPWR_IN: C3.1, C4.1, U2.1 (PWR_IN), U2.2 (PWR_IN), U2.3 (PWR_IN), U3.1 (VIN), U3.7 (MODE), U4.2 (VIN)
GNDPWR: C1.1, C2.2, C4.2, R2.2, R17.1, U2.4 (GND), U2.8 (GND), U3.2 (GND), U3.3 (GND), U3.6 (GND), U4.4 (VOUT), U4.5 (VOUT)
unnamed: R2.1, R3.1
unnamed: R18.1, R20.1
unnamed: R1.2, R3.2, U3.5 (FB)
unnamed: R17.2, R20.2, U4.6 (FB)
unnamed: C9.1, U4.8 (SS/TR)
VDDA: C2.1, R1.1, U2.9 (VDDA), U2.10 (VDDA), U3.4 (VOUT)
VSSA: C1.2, C3.2, C9.2, R18.2, U2.6 (VSSA), U2.7 (VSSA), U4.3 (GND), U4.9 (GND)

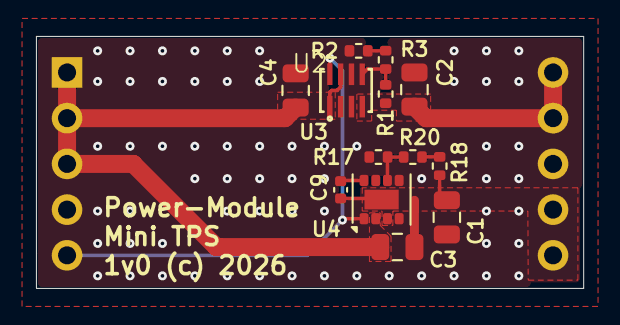
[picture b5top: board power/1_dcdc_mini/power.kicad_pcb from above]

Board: 2 copper layers, 30.4 x 14.0 mm, 14 parts (0 on the bottom side), 10 nets.

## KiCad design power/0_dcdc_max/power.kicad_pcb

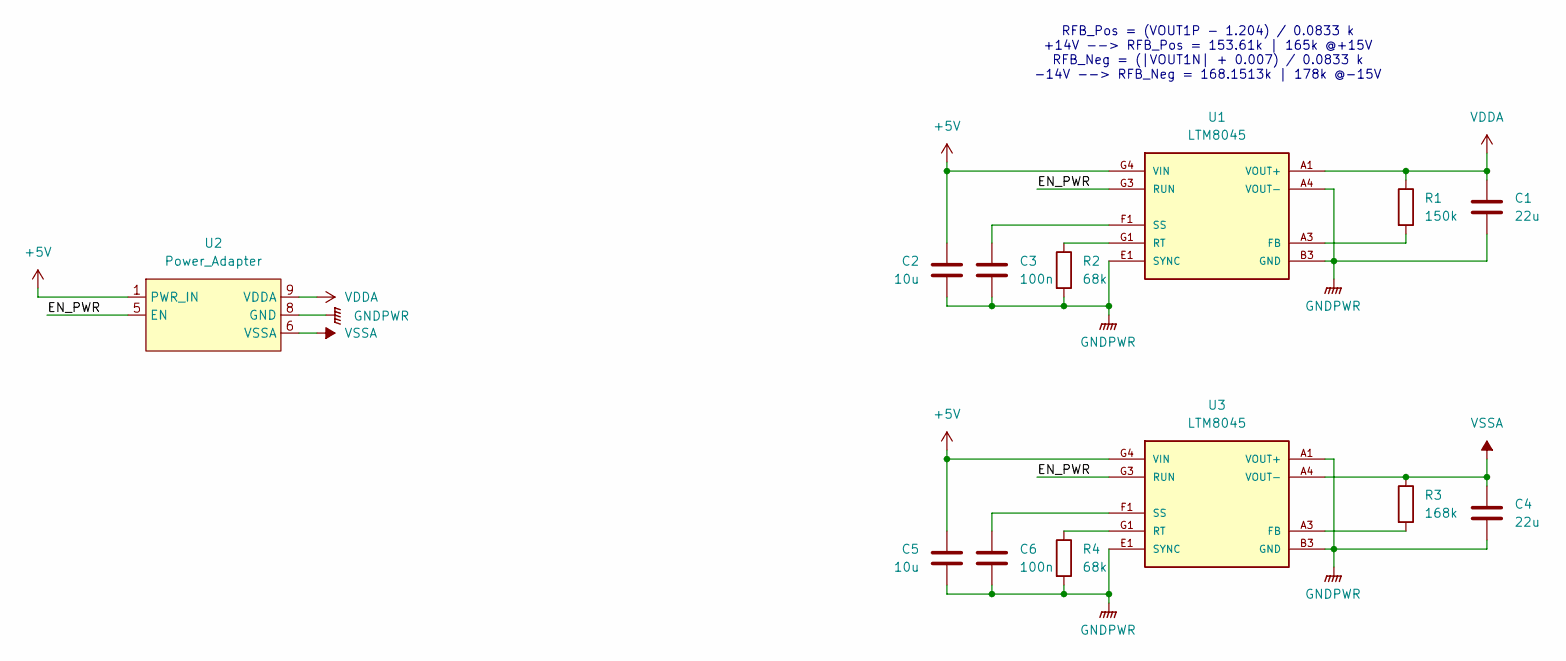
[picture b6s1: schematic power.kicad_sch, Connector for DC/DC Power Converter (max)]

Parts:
C1, C4: 22u; C_1206_3216Metric
C2, C5: 10u; C_0805_2012Metric
C3, C6: 100n; C_0402_1005Metric
R1: 150k; R_0402_1005Metric
R2, R4: 68k; R_0402_1005Metric
R3: 168k; R_0402_1005Metric
U1, U3: LTM8045; BGA40C127P5X8_625X1125X512N
U2: Power_Adapter; power_adapter

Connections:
+5V: C2.1, C5.1, U1.G4 (VIN), U1.G5 (VIN), U1.H4 (VIN), U1.H5 (VIN), U2.1 (PWR_IN), U2.2 (PWR_IN), U2.3 (PWR_IN), U3.G4 (VIN), U3.G5 (VIN), U3.H4 (VIN), U3.H5 (VIN)
/EN_PWR: U1.G3 (RUN), U2.5 (EN), U3.G3 (RUN)
GNDPWR: C1.2, C2.2, C3.2, C4.2, C5.2, C6.2, R2.2, R4.2, U1.A4 (VOUT-), U1.A5 (VOUT-), U1.B3 (GND), U1.B4 (VOUT-), U1.B5 (VOUT-), U1.C1 (GND), U1.C2 (GND), U1.C3 (GND), U1.C4 (GND), U1.C5 (GND), U1.D1 (GND), U1.D2 (GND), U1.D3 (GND), U1.D4 (GND), U1.D5 (GND), U1.E1 (SYNC), U1.E2 (GND), U1.E3 (GND), U1.E4 (GND), U1.E5 (GND), U1.F2 (GND), U1.F3 (GND), U1.F4 (GND), U1.F5 (GND), U1.G2 (GND), U1.H1 (GND), U1.H2 (GND), U1.H3 (GND), U2.4 (GND), U2.8 (GND), U3.A1 (VOUT+), U3.A2 (VOUT+), U3.B1 (VOUT+), U3.B2 (VOUT+), U3.B3 (GND), U3.C1 (GND), U3.C2 (GND), U3.C3 (GND), U3.C4 (GND), U3.C5 (GND), U3.D1 (GND), U3.D2 (GND), U3.D3 (GND), U3.D4 (GND), U3.D5 (GND), U3.E1 (SYNC), U3.E2 (GND), U3.E3 (GND), U3.E4 (GND), U3.E5 (GND), U3.F2 (GND), U3.F3 (GND), U3.F4 (GND), U3.F5 (GND), U3.G2 (GND), U3.H1 (GND), U3.H2 (GND), U3.H3 (GND)
unnamed: R1.2, U1.A3 (FB)
unnamed: R2.1, U1.G1 (RT)
unnamed: C3.1, U1.F1 (SS)
unnamed: R3.2, U3.A3 (FB)
unnamed: R4.1, U3.G1 (RT)
unnamed: C6.1, U3.F1 (SS)
VDDA: C1.1, R1.1, U1.A1 (VOUT+), U1.A2 (VOUT+), U1.B1 (VOUT+), U1.B2 (VOUT+), U2.9 (VDDA), U2.10 (VDDA)
VSSA: C4.1, R3.1, U2.6 (VSSA), U2.7 (VSSA), U3.A4 (VOUT-), U3.A5 (VOUT-), U3.B4 (VOUT-), U3.B5 (VOUT-)

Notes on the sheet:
RFB_Pos = (VOUT1P - 1.204) / 0.0833 k +14V --> RFB_Pos = 153.61k | 165k @+15V RFB_Neg = (|VOUT1N| + 0.007) / 0.0833 k -14V --> RFB_Neg = 168.1513k | 178k @-15V

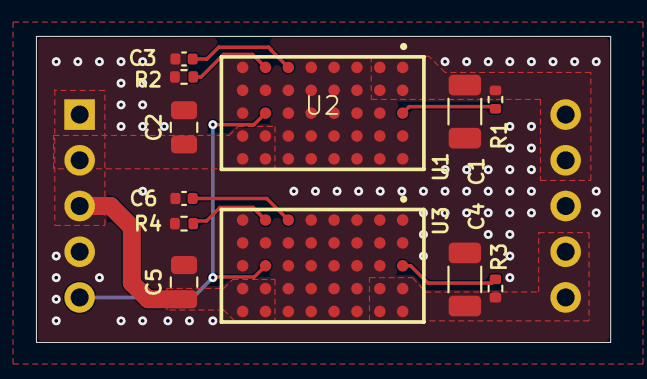
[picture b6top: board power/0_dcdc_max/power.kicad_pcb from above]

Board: 2 copper layers, 31.9 x 17.0 mm, 13 parts (0 on the bottom side), 11 nets.

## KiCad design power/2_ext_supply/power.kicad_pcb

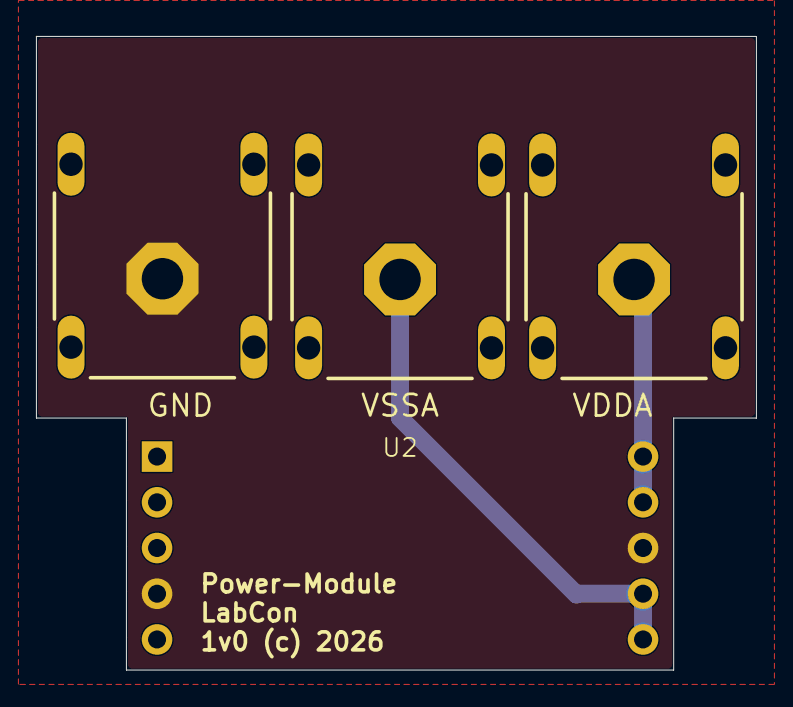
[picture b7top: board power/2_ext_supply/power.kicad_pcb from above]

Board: 2 copper layers, 40.0 x 35.2 mm, 4 parts (0 on the bottom side), 3 nets.

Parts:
U2: Power_Adapter; power_adapter
X1: GND; 4MM_SHROUDED_BK
X2: VDDA; 4MM_SHROUDED_RD
X3: VSSA; 4MM_SHROUDED_BL

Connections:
GND: U2.4 (GND), U2.8 (GND), X1.1 (VAL_1)
unnamed: U2.9 (VDDA), U2.10 (VDDA), X2.1 (VAL_1)
unnamed: U2.6 (VSSA), U2.7 (VSSA), X3.1 (VAL_1)
